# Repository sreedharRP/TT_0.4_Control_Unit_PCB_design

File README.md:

# TT_0.4_Control_Unit_PCB_design

This repository consist of 
 * PCB board design of TT_0.4 AUV's control unit.
 * Electrical Connection digram and communication.
 * EDA files and 3D models

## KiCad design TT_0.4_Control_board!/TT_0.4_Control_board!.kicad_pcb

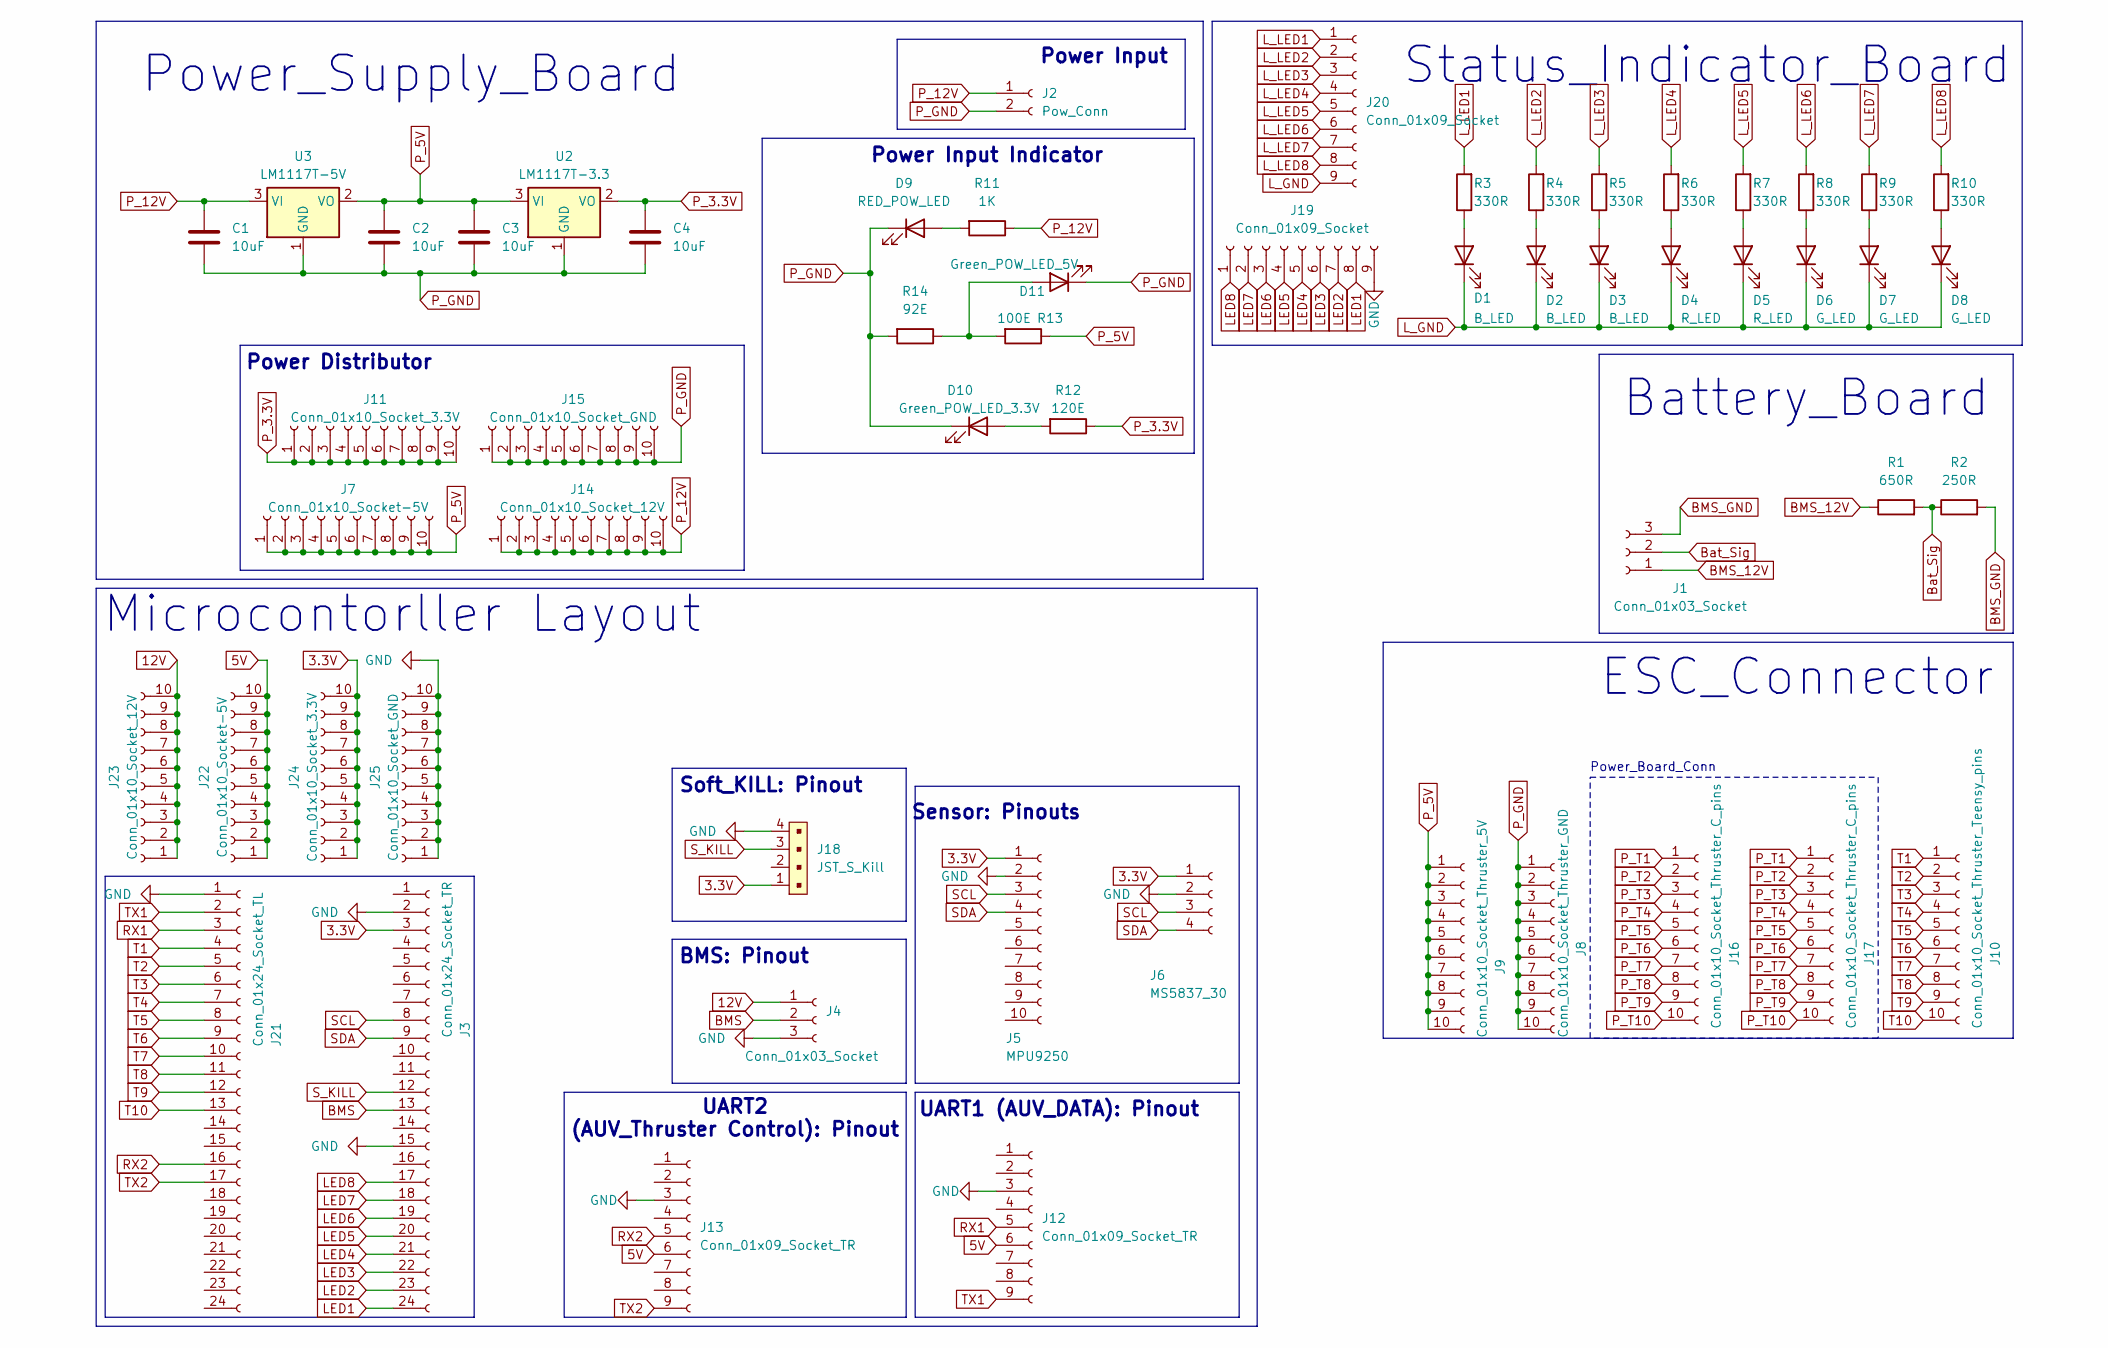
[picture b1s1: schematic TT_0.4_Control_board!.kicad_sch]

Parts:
C1, C2, C3, C4: 10uF; C_Disc_D7.5mm_W5.0mm_P5.00mm
D1, D2, D3: B_LED; LED_D5.0mm
D4, D5: R_LED; LED_D5.0mm
D6, D7, D8: G_LED; LED_D5.0mm
D9: RED_POW_LED; LED_D5.0mm
D10: Green_POW_LED_3.3V; LED_D5.0mm
D11: Green_POW_LED_5V; LED_D5.0mm
J1, J4: Conn_01x03_Socket; PinSocket_1x03_P2.54mm_Vertical
J2: Pow_Conn; TerminalBlock_MaiXu_MX126-5.0-02P_1x02_P5.00mm
J3: Conn_01x24_Socket_TR; PinSocket_1x24_P2.54mm_Vertical
J5: MPU9250; PinSocket_1x10_P2.54mm_Vertical
J6: MS5837_30; PinSocket_1x04_P2.54mm_Vertical
J7, J22: Conn_01x10_Socket-5V; PinSocket_1x10_P2.54mm_Vertical
J8: Conn_01x10_Socket_Thruster_GND; PinSocket_1x10_P2.54mm_Vertical
J9: Conn_01x10_Socket_Thruster_5V; PinSocket_1x10_P2.54mm_Vertical
J10: Conn_01x10_Socket_Thruster_Teensy_pins; PinSocket_1x10_P2.54mm_Vertical
J11, J24: Conn_01x10_Socket_3.3V; PinSocket_1x10_P2.54mm_Vertical
J12, J13: Conn_01x09_Socket_TR; PinSocket_1x09_P2.54mm_Vertical
J14, J23: Conn_01x10_Socket_12V; PinSocket_1x10_P2.54mm_Vertical
J15, J25: Conn_01x10_Socket_GND; PinSocket_1x10_P2.54mm_Vertical
J16, J17: Conn_01x10_Socket_Thruster_C_pins; PinSocket_1x10_P2.54mm_Vertical
J18: JST_S_Kill; PinHeader_1x4_P2.5mm_Drill1.1mm; MPN B4B-XH-A(LF)(SN); Digi-Key_PN 455-2249-ND
J19, J20: Conn_01x09_Socket; PinHeader_1x09_P2.54mm_Vertical
J21: Conn_01x24_Socket_TL; PinSocket_1x24_P2.54mm_Vertical
R1: 650R; R_Axial_DIN0309_L9.0mm_D3.2mm_P15.24mm_Horizontal
R2: 250R; R_Axial_DIN0309_L9.0mm_D3.2mm_P15.24mm_Horizontal
R3, R4, R5, R6, R7, R8, R9, R10: 330R; R_Axial_DIN0207_L6.3mm_D2.5mm_P7.62mm_Horizontal
R11: 1K; R_Axial_DIN0414_L11.9mm_D4.5mm_P15.24mm_Horizontal
R12: 120E; R_Axial_DIN0207_L6.3mm_D2.5mm_P7.62mm_Horizontal
R13: 100E; R_Axial_DIN0207_L6.3mm_D2.5mm_P7.62mm_Horizontal
R14: 92E; R_Axial_DIN0207_L6.3mm_D2.5mm_P7.62mm_Horizontal
U2: LM1117T-3.3; SOT-223-3_TabPin2
U3: LM1117T-5V; SOT-223-3_TabPin2

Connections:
3.3V: J3.3, J5.1, J6.1, J18.1, J24.1, J24.2, J24.3, J24.4, J24.5, J24.6, J24.7, J24.8, J24.9, J24.10
5V: J12.6, J13.6, J22.1, J22.2, J22.3, J22.4, J22.5, J22.6, J22.7, J22.8, J22.9, J22.10
12V: J4.1, J23.1, J23.2, J23.3, J23.4, J23.5, J23.6, J23.7, J23.8, J23.9, J23.10
BMS: J3.13, J4.2
BMS_12V: J1.1, R1.1
BMS_GND: J1.3, R2.2
Bat_Sig: J1.2, R1.2, R2.1
GND: J3.2, J3.15, J4.3, J5.2, J6.2, J12.3, J13.3, J18.4, J19.9, J21.1, J25.1, J25.2, J25.3, J25.4, J25.5, J25.6, J25.7, J25.8, J25.9, J25.10
LED1: J3.24, J19.8
LED2: J3.23, J19.7
LED3: J3.22, J19.6
LED4: J3.21, J19.5
LED5: J3.20, J19.4
LED6: J3.19, J19.3
LED7: J3.18, J19.2
LED8: J3.17, J19.1
L_GND: D1.1 (K), D2.1 (K), D3.1 (K), D4.1 (K), D5.1 (K), D6.1 (K), D7.1 (K), D8.1 (K), J20.9
L_LED1: J20.1, R3.2
L_LED2: J20.2, R4.2
L_LED3: J20.3, R5.2
L_LED4: J20.4, R6.2
L_LED5: J20.5, R7.2
L_LED6: J20.6, R8.2
L_LED7: J20.7, R9.2
L_LED8: J20.8, R10.2
unnamed: D1.2 (A), R3.1
unnamed: D2.2 (A), R4.1
unnamed: D3.2 (A), R5.1
unnamed: D4.2 (A), R6.1
unnamed: D5.2 (A), R7.1
unnamed: D6.2 (A), R8.1
unnamed: D7.2 (A), R9.1
unnamed: D8.2 (A), R10.1
unnamed: D9.2 (A), R11.2
unnamed: D10.2 (A), R12.2
unnamed: D11.2 (A), R13.2, R14.1
P_3.3V: C4.1, J11.1, J11.2, J11.3, J11.4, J11.5, J11.6, J11.7, J11.8, J11.9, J11.10, R12.1, U2.2 (VO)
P_5V: C2.1, C3.1, J7.1, J7.2, J7.3, J7.4, J7.5, J7.6, J7.7, J7.8, J7.9, J7.10, J9.1, J9.2, J9.3, J9.4, J9.5, J9.6, J9.7, J9.8, J9.9, J9.10, R13.1, U2.3 (VI), U3.2 (VO)
P_12V: C1.1, J2.1, J14.1, J14.2, J14.3, J14.4, J14.5, J14.6, J14.7, J14.8, J14.9, J14.10, R11.1, U3.3 (VI)
P_GND: C1.2, C2.2, C3.2, C4.2, D9.1 (K), D10.1 (K), D11.1 (K), J2.2, J8.1, J8.2, J8.3, J8.4, J8.5, J8.6, J8.7, J8.8, J8.9, J8.10, J15.1, J15.2, J15.3, J15.4, J15.5, J15.6, J15.7, J15.8, J15.9, J15.10, R14.2, U2.1 (GND), U3.1 (GND)
P_T1: J16.1, J17.1
P_T2: J16.2, J17.2
P_T3: J16.3, J17.3
P_T4: J16.4, J17.4
P_T5: J16.5, J17.5
P_T6: J16.6, J17.6
P_T7: J16.7, J17.7
P_T8: J16.8, J17.8
P_T9: J16.9, J17.9
P_T10: J16.10, J17.10
RX1: J12.5, J21.3
RX2: J13.5, J21.16
SCL: J3.8, J5.3, J6.3
SDA: J3.9, J5.4, J6.4
S_KILL: J3.12, J18.3
T1: J10.1, J21.4
T2: J10.2, J21.5
T3: J10.3, J21.6
T4: J10.4, J21.7
T5: J10.5, J21.8
T6: J10.6, J21.9
T7: J10.7, J21.10
T8: J10.8, J21.11
T9: J10.9, J21.12
T10: J10.10, J21.13
TX1: J12.9, J21.2
TX2: J13.9, J21.17

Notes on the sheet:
BMS: Pinout
UART1 (AUV_DATA): Pinout
Battery_Board
Microcontorller Layout
Soft_KILL: Pinout
Power Input Indicator
ESC_Connector
Power Distributor
UART2 (AUV_Thruster Control): Pinout
Status_Indicator_Board
Power Input
Power_Supply_Board
Sensor: Pinouts
Power_Board_Conn

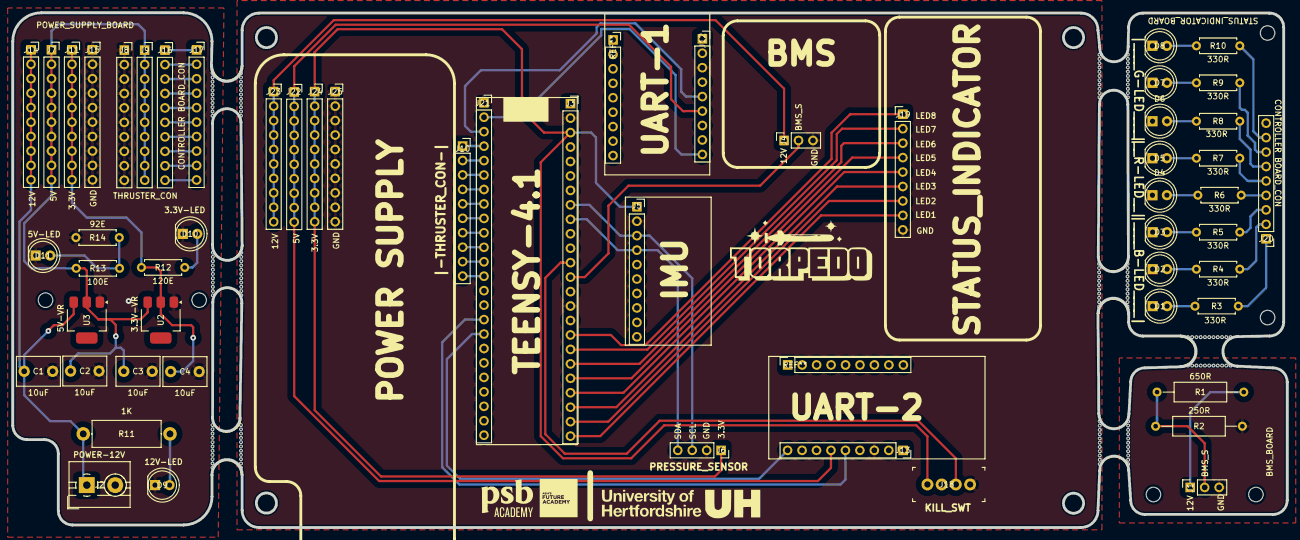
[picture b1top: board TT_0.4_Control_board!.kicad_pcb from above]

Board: 2 copper layers, 224.0 x 90.4 mm, 63 parts (0 on the bottom side), 67 nets.

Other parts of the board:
mouse-bite-5mm-slot, mouse-bite-5mm-slot#2, mouse-bite-5mm-slot#3, mouse-bite-5mm-slot#4, mouse-bite-5mm-slot#5, mouse-bite-5mm-slot#6, mouse-bite-5mm-slot#7: VAL**; mouse-bite-5mm-slot

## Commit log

2025-01-03 PCB board
    Designing of PCB board
2025-01-03 Update of readme
2025-01-03 update of files
2025-02-20 PCB Update
2025-07-29 Final_PCB_Design
    This push final, updated push TT-0.4:Controller
